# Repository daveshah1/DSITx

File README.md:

# MIPI DSI FPGA LCD Interface

This is a work-in-progress core to interface advanced MIPI DSI displays with a Xilinx
7-series FPGA. The current display target is the Sony Z5 Premium LCD (AUO H546UAN01.0 or Sharp LS055D1SX05)
which is a  5.5" 4k (2160x3840) LCD. At the moment I am running it in a mode where content is upscaled by the panel
from 1080x1920, as 4k content must be compressed using VESA DSC or Qualcomm FBC. I am working on an encoder for the former.

The only DSI mode currently supported is Command Mode, Video Mode is still being worked on and is not as well documented for the target panels. This
panel works in dual DSI mode, so two transmitters are used each transmitting half of each line. Single-link command mode panels would also work, with
by only instantiating one `dsi_tx_cmd_mode_top`.

A demo project is included for the afforementioned panel and config. It was designed for an FMC breakout board I've built for the Genesys 2 development
board with a Kintex-7 FPGA. Unfortunately a signal integrity issue on this board means I have to run the DSI link at its lowest rate, 200Mbps, which limits
the framerate to about 30fps. Nonetheless, the design files for this board are included if you want a circuit to run the display, although in any system
you develop the MIPI DSI translator resistors should be located much closer to the FPGA to avoid the issues I've had.

The final intended use of this interface is for a larger project I am working on, the [openMixR](https://github.com/daveshah1/openMixR) 4k headset.

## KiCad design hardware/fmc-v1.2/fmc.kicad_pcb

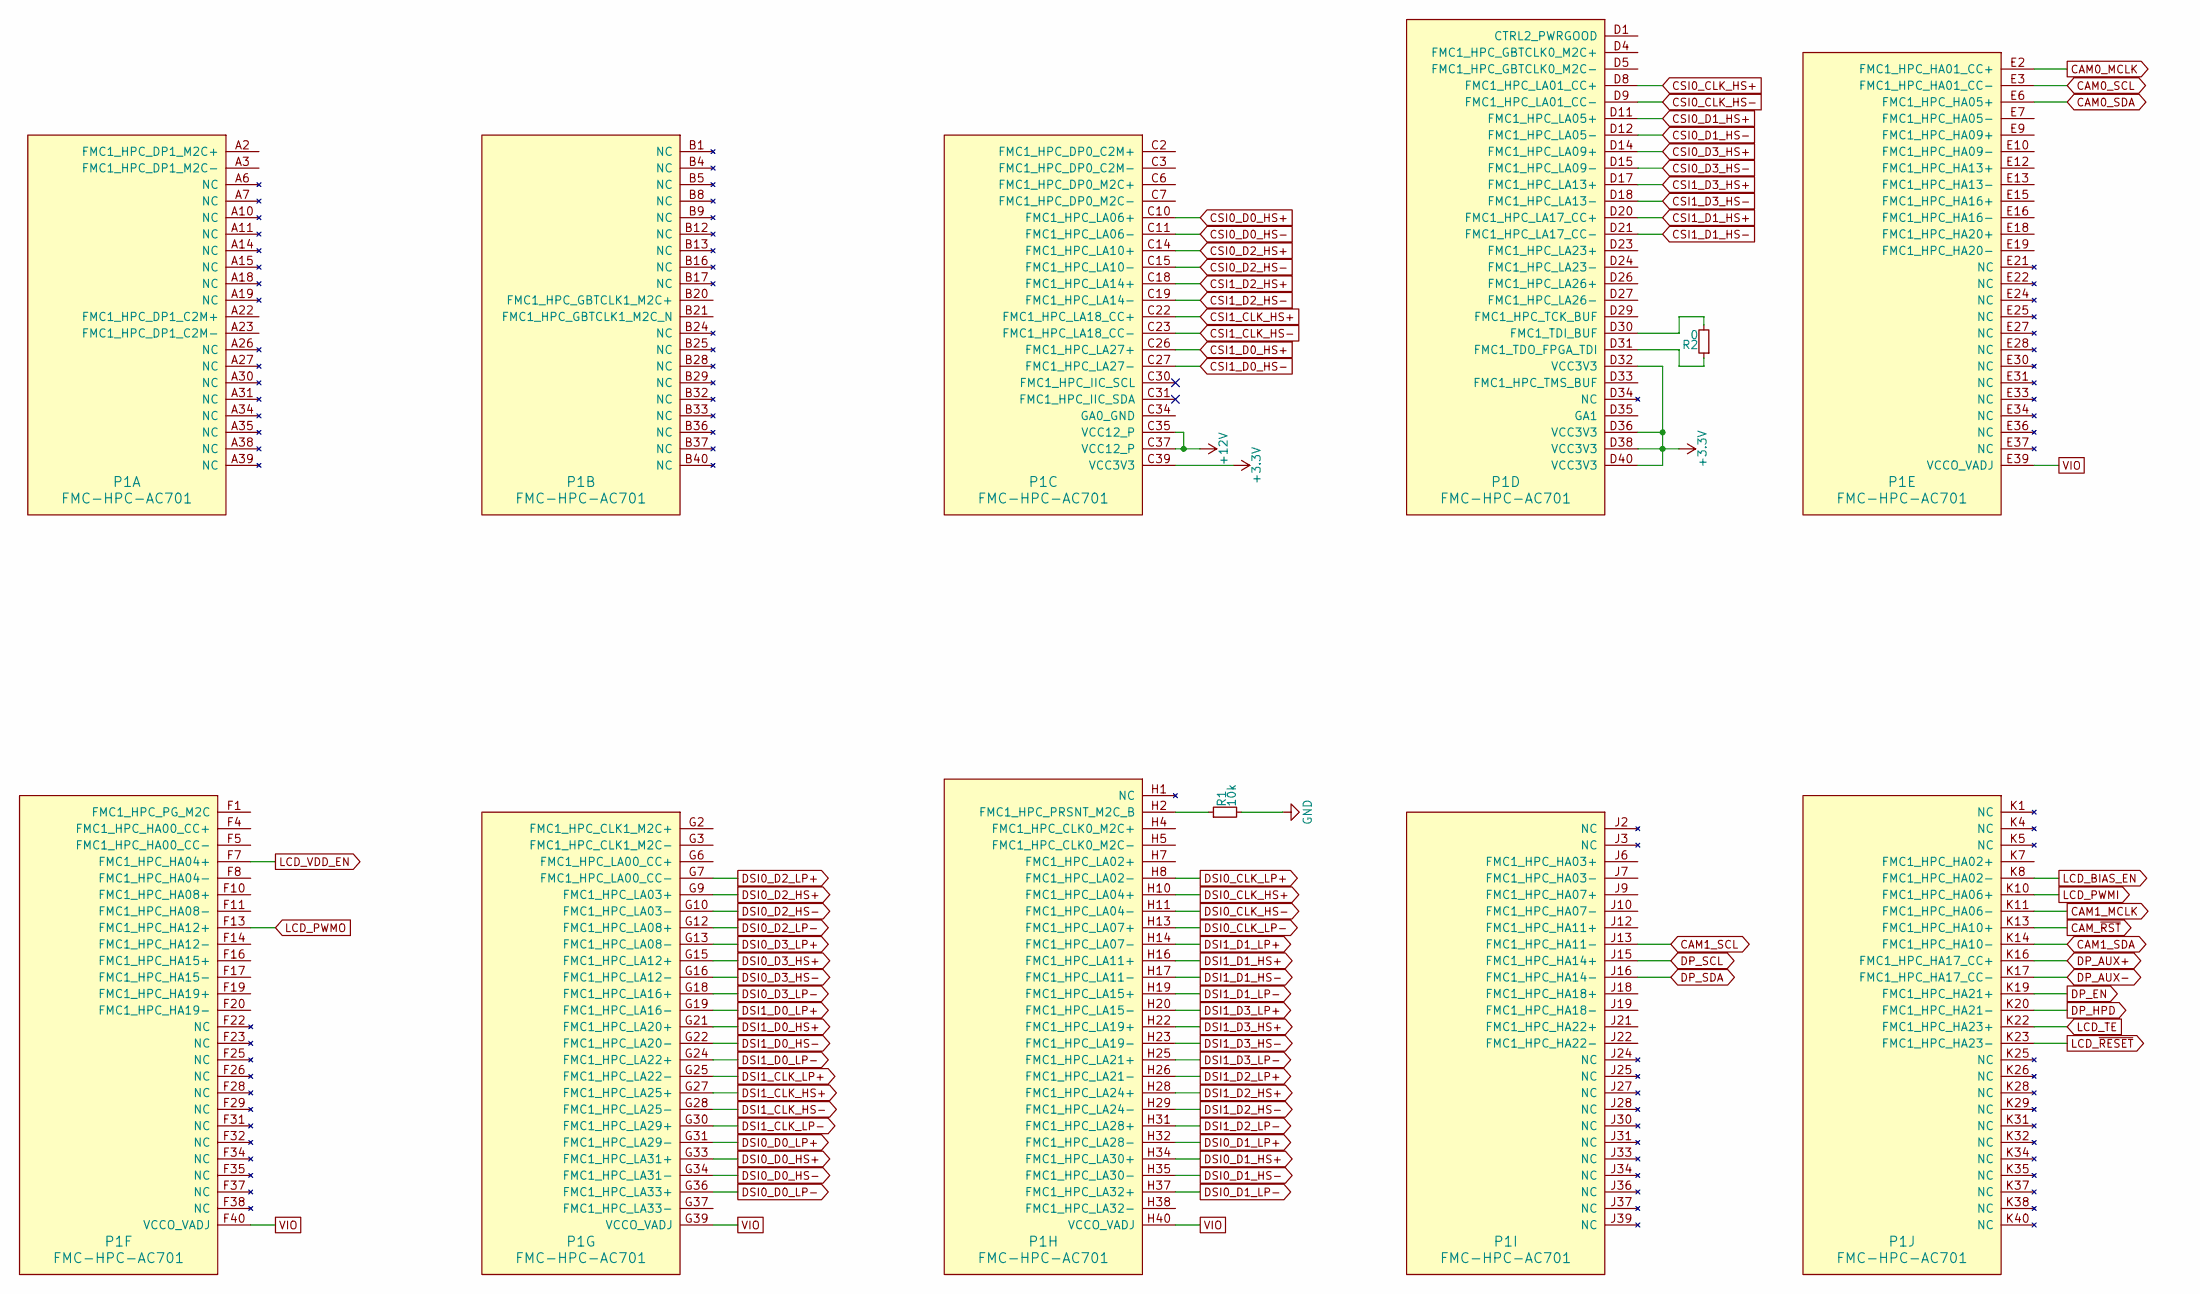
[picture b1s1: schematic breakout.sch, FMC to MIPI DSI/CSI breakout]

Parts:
P1: FMC-HPC-AC701; ASP-134488-01
R1: 10k; R_0402
R2: 0; R_0402

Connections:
+3V3: P1.C39 (VCC3V3), P1.D32 (VCC3V3), P1.D36 (VCC3V3), P1.D38 (VCC3V3), P1.D40 (VCC3V3); also elsewhere on the board
+12V: P1.C35 (VCC12_P), P1.C37 (VCC12_P); also elsewhere on the board
CAM0_MCLK: P1.E2 (FMC1_HPC_HA01_CC+); also elsewhere on the board
CAM0_SCL: P1.E3 (FMC1_HPC_HA01_CC-); also elsewhere on the board
CAM0_SDA: P1.E6 (FMC1_HPC_HA05+); also elsewhere on the board
CAM1_MCLK: P1.K11 (FMC1_HPC_HA06-); also elsewhere on the board
CAM1_SCL: P1.J13 (FMC1_HPC_HA11-); also elsewhere on the board
CAM1_SDA: P1.K14 (FMC1_HPC_HA10-); also elsewhere on the board
CAM_~RST: P1.K13 (FMC1_HPC_HA10+); also elsewhere on the board
CSI0_CLK_HS+: P1.D8 (FMC1_HPC_LA01_CC+); also elsewhere on the board
CSI0_CLK_HS-: P1.D9 (FMC1_HPC_LA01_CC-); also elsewhere on the board
CSI0_D0_HS+: P1.C10 (FMC1_HPC_LA06+); also elsewhere on the board
CSI0_D0_HS-: P1.C11 (FMC1_HPC_LA06-); also elsewhere on the board
CSI0_D1_HS+: P1.D11 (FMC1_HPC_LA05+); also elsewhere on the board
CSI0_D1_HS-: P1.D12 (FMC1_HPC_LA05-); also elsewhere on the board
CSI0_D2_HS+: P1.C14 (FMC1_HPC_LA10+); also elsewhere on the board
CSI0_D2_HS-: P1.C15 (FMC1_HPC_LA10-); also elsewhere on the board
CSI0_D3_HS+: P1.D14 (FMC1_HPC_LA09+); also elsewhere on the board
CSI0_D3_HS-: P1.D15 (FMC1_HPC_LA09-); also elsewhere on the board
CSI1_CLK_HS+: P1.C22 (FMC1_HPC_LA18_CC+); also elsewhere on the board
CSI1_CLK_HS-: P1.C23 (FMC1_HPC_LA18_CC-); also elsewhere on the board
CSI1_D0_HS+: P1.C26 (FMC1_HPC_LA27+); also elsewhere on the board
CSI1_D0_HS-: P1.C27 (FMC1_HPC_LA27-); also elsewhere on the board
CSI1_D1_HS+: P1.D20 (FMC1_HPC_LA17_CC+); also elsewhere on the board
CSI1_D1_HS-: P1.D21 (FMC1_HPC_LA17_CC-); also elsewhere on the board
CSI1_D2_HS+: P1.C18 (FMC1_HPC_LA14+); also elsewhere on the board
CSI1_D2_HS-: P1.C19 (FMC1_HPC_LA14-); also elsewhere on the board
CSI1_D3_HS+: P1.D17 (FMC1_HPC_LA13+); also elsewhere on the board
CSI1_D3_HS-: P1.D18 (FMC1_HPC_LA13-); also elsewhere on the board
DSI0_CLK_HS+: P1.H10 (FMC1_HPC_LA04+); also elsewhere on the board
DSI0_CLK_HS-: P1.H11 (FMC1_HPC_LA04-); also elsewhere on the board
DSI0_CLK_LP+: P1.H8 (FMC1_HPC_LA02-); also elsewhere on the board
DSI0_CLK_LP-: P1.H13 (FMC1_HPC_LA07+); also elsewhere on the board
DSI0_D0_HS+: P1.G33 (FMC1_HPC_LA31+); also elsewhere on the board
DSI0_D0_HS-: P1.G34 (FMC1_HPC_LA31-); also elsewhere on the board
DSI0_D0_LP+: P1.G31 (FMC1_HPC_LA29-); also elsewhere on the board
DSI0_D0_LP-: P1.G36 (FMC1_HPC_LA33+); also elsewhere on the board
DSI0_D1_HS+: P1.H34 (FMC1_HPC_LA30+); also elsewhere on the board
DSI0_D1_HS-: P1.H35 (FMC1_HPC_LA30-); also elsewhere on the board
DSI0_D1_LP+: P1.H32 (FMC1_HPC_LA28-); also elsewhere on the board
DSI0_D1_LP-: P1.H37 (FMC1_HPC_LA32+); also elsewhere on the board
DSI0_D2_HS+: P1.G9 (FMC1_HPC_LA03+); also elsewhere on the board
DSI0_D2_HS-: P1.G10 (FMC1_HPC_LA03-); also elsewhere on the board
DSI0_D2_LP+: P1.G7 (FMC1_HPC_LA00_CC-); also elsewhere on the board
DSI0_D2_LP-: P1.G12 (FMC1_HPC_LA08+); also elsewhere on the board
DSI0_D3_HS+: P1.G15 (FMC1_HPC_LA12+); also elsewhere on the board
DSI0_D3_HS-: P1.G16 (FMC1_HPC_LA12-); also elsewhere on the board
DSI0_D3_LP+: P1.G13 (FMC1_HPC_LA08-); also elsewhere on the board
DSI0_D3_LP-: P1.G18 (FMC1_HPC_LA16+); also elsewhere on the board
DSI1_CLK_HS+: P1.G27 (FMC1_HPC_LA25+); also elsewhere on the board
DSI1_CLK_HS-: P1.G28 (FMC1_HPC_LA25-); also elsewhere on the board
DSI1_CLK_LP+: P1.G25 (FMC1_HPC_LA22-); also elsewhere on the board
DSI1_CLK_LP-: P1.G30 (FMC1_HPC_LA29+); also elsewhere on the board
DSI1_D0_HS+: P1.G21 (FMC1_HPC_LA20+); also elsewhere on the board
DSI1_D0_HS-: P1.G22 (FMC1_HPC_LA20-); also elsewhere on the board
DSI1_D0_LP+: P1.G19 (FMC1_HPC_LA16-); also elsewhere on the board
DSI1_D0_LP-: P1.G24 (FMC1_HPC_LA22+); also elsewhere on the board
DSI1_D1_HS+: P1.H16 (FMC1_HPC_LA11+); also elsewhere on the board
DSI1_D1_HS-: P1.H17 (FMC1_HPC_LA11-); also elsewhere on the board
DSI1_D1_LP+: P1.H14 (FMC1_HPC_LA07-); also elsewhere on the board
DSI1_D1_LP-: P1.H19 (FMC1_HPC_LA15+); also elsewhere on the board
DSI1_D2_HS+: P1.H28 (FMC1_HPC_LA24+); also elsewhere on the board
DSI1_D2_HS-: P1.H29 (FMC1_HPC_LA24-); also elsewhere on the board
DSI1_D2_LP+: P1.H26 (FMC1_HPC_LA21-); also elsewhere on the board
DSI1_D2_LP-: P1.H31 (FMC1_HPC_LA28+); also elsewhere on the board
DSI1_D3_HS+: P1.H22 (FMC1_HPC_LA19+); also elsewhere on the board
DSI1_D3_HS-: P1.H23 (FMC1_HPC_LA19-); also elsewhere on the board
DSI1_D3_LP+: P1.H20 (FMC1_HPC_LA15-); also elsewhere on the board
DSI1_D3_LP-: P1.H25 (FMC1_HPC_LA21+); also elsewhere on the board
GND: R1.2; also elsewhere on the board
LCD_BIAS_EN: P1.K8 (FMC1_HPC_HA02-); also elsewhere on the board
LCD_PWMI: P1.K10 (FMC1_HPC_HA06+); also elsewhere on the board
LCD_TE: P1.K22 (FMC1_HPC_HA23+); also elsewhere on the board
LCD_VDD_EN: P1.F7 (FMC1_HPC_HA04+); also elsewhere on the board
LCD_~RESET: P1.K23 (FMC1_HPC_HA23-); also elsewhere on the board
unnamed: P1.D30 (FMC1_TDI_BUF), R2.2
unnamed: P1.D31 (FMC1_TDO_FPGA_TDI), R2.1
unnamed: P1.H2 (FMC1_HPC_PRSNT_M2C_B), R1.1
VIO: P1.E39 (VCCO_VADJ), P1.F40 (VCCO_VADJ), P1.G39 (VCCO_VADJ), P1.H40 (VCCO_VADJ); also elsewhere on the board

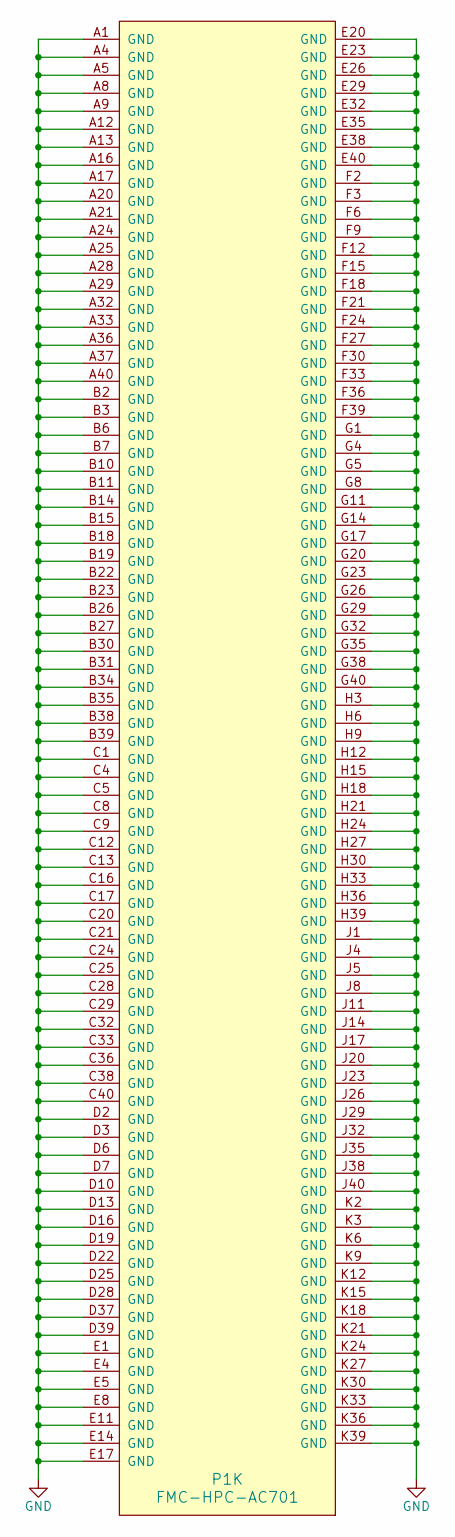
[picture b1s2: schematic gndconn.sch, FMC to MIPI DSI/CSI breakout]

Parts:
P1: FMC-HPC-AC701; ASP-134488-01

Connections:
GND: P1.A1 (GND), P1.A4 (GND), P1.A5 (GND), P1.A8 (GND), P1.A9 (GND), P1.A12 (GND), P1.A13 (GND), P1.A16 (GND), P1.A17 (GND), P1.A20 (GND), P1.A21 (GND), P1.A24 (GND), P1.A25 (GND), P1.A28 (GND), P1.A29 (GND), P1.A32 (GND), P1.A33 (GND), P1.A36 (GND), P1.A37 (GND), P1.A40 (GND), P1.B2 (GND), P1.B3 (GND), P1.B6 (GND), P1.B7 (GND), P1.B10 (GND), P1.B11 (GND), P1.B14 (GND), P1.B15 (GND), P1.B18 (GND), P1.B19 (GND), P1.B22 (GND), P1.B23 (GND), P1.B26 (GND), P1.B27 (GND), P1.B30 (GND), P1.B31 (GND), P1.B34 (GND), P1.B35 (GND), P1.B38 (GND), P1.B39 (GND), P1.C1 (GND), P1.C4 (GND), P1.C5 (GND), P1.C8 (GND), P1.C9 (GND), P1.C12 (GND), P1.C13 (GND), P1.C16 (GND), P1.C17 (GND), P1.C20 (GND), P1.C21 (GND), P1.C24 (GND), P1.C25 (GND), P1.C28 (GND), P1.C29 (GND), P1.C32 (GND), P1.C33 (GND), P1.C36 (GND), P1.C38 (GND), P1.C40 (GND), P1.D2 (GND), P1.D3 (GND), P1.D6 (GND), P1.D7 (GND), P1.D10 (GND), P1.D13 (GND), P1.D16 (GND), P1.D19 (GND), P1.D22 (GND), P1.D25 (GND), P1.D28 (GND), P1.D37 (GND), P1.D39 (GND), P1.E1 (GND), P1.E4 (GND), P1.E5 (GND), P1.E8 (GND), P1.E11 (GND), P1.E14 (GND), P1.E17 (GND), P1.E20 (GND), P1.E23 (GND), P1.E26 (GND), P1.E29 (GND), P1.E32 (GND), P1.E35 (GND), P1.E38 (GND), P1.E40 (GND), P1.F2 (GND), P1.F3 (GND), P1.F6 (GND), P1.F9 (GND), P1.F12 (GND), P1.F15 (GND), P1.F18 (GND), P1.F21 (GND), P1.F24 (GND), P1.F27 (GND), P1.F30 (GND), P1.F33 (GND), P1.F36 (GND), P1.F39 (GND), P1.G1 (GND), P1.G4 (GND), P1.G5 (GND), P1.G8 (GND), P1.G11 (GND), P1.G14 (GND), P1.G17 (GND), P1.G20 (GND), P1.G23 (GND), P1.G26 (GND), P1.G29 (GND), P1.G32 (GND), P1.G35 (GND), P1.G38 (GND), P1.G40 (GND), P1.H3 (GND), P1.H6 (GND), P1.H9 (GND), P1.H12 (GND), P1.H15 (GND), P1.H18 (GND), P1.H21 (GND), P1.H24 (GND), P1.H27 (GND), P1.H30 (GND), P1.H33 (GND), P1.H36 (GND), P1.H39 (GND), P1.J1 (GND), P1.J4 (GND), P1.J5 (GND), P1.J8 (GND), P1.J11 (GND), P1.J14 (GND), P1.J17 (GND), P1.J20 (GND), P1.J23 (GND), P1.J26 (GND), P1.J29 (GND), P1.J32 (GND), P1.J35 (GND), P1.J38 (GND), P1.J40 (GND), P1.K2 (GND), P1.K3 (GND), P1.K6 (GND), P1.K9 (GND), P1.K12 (GND), P1.K15 (GND), P1.K18 (GND), P1.K21 (GND), P1.K24 (GND), P1.K27 (GND), P1.K30 (GND), P1.K33 (GND), P1.K36 (GND), P1.K39 (GND); also elsewhere on the board

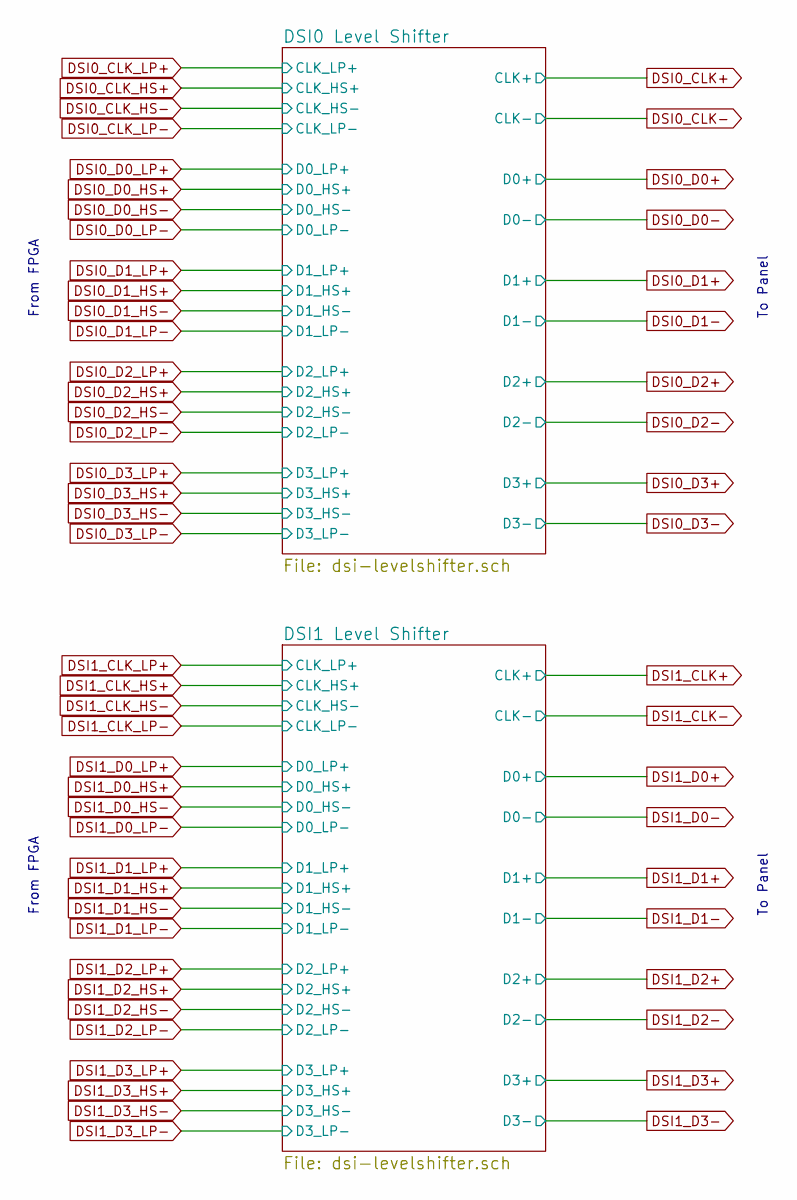
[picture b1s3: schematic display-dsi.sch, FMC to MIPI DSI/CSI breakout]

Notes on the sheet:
From FPGA
To Panel

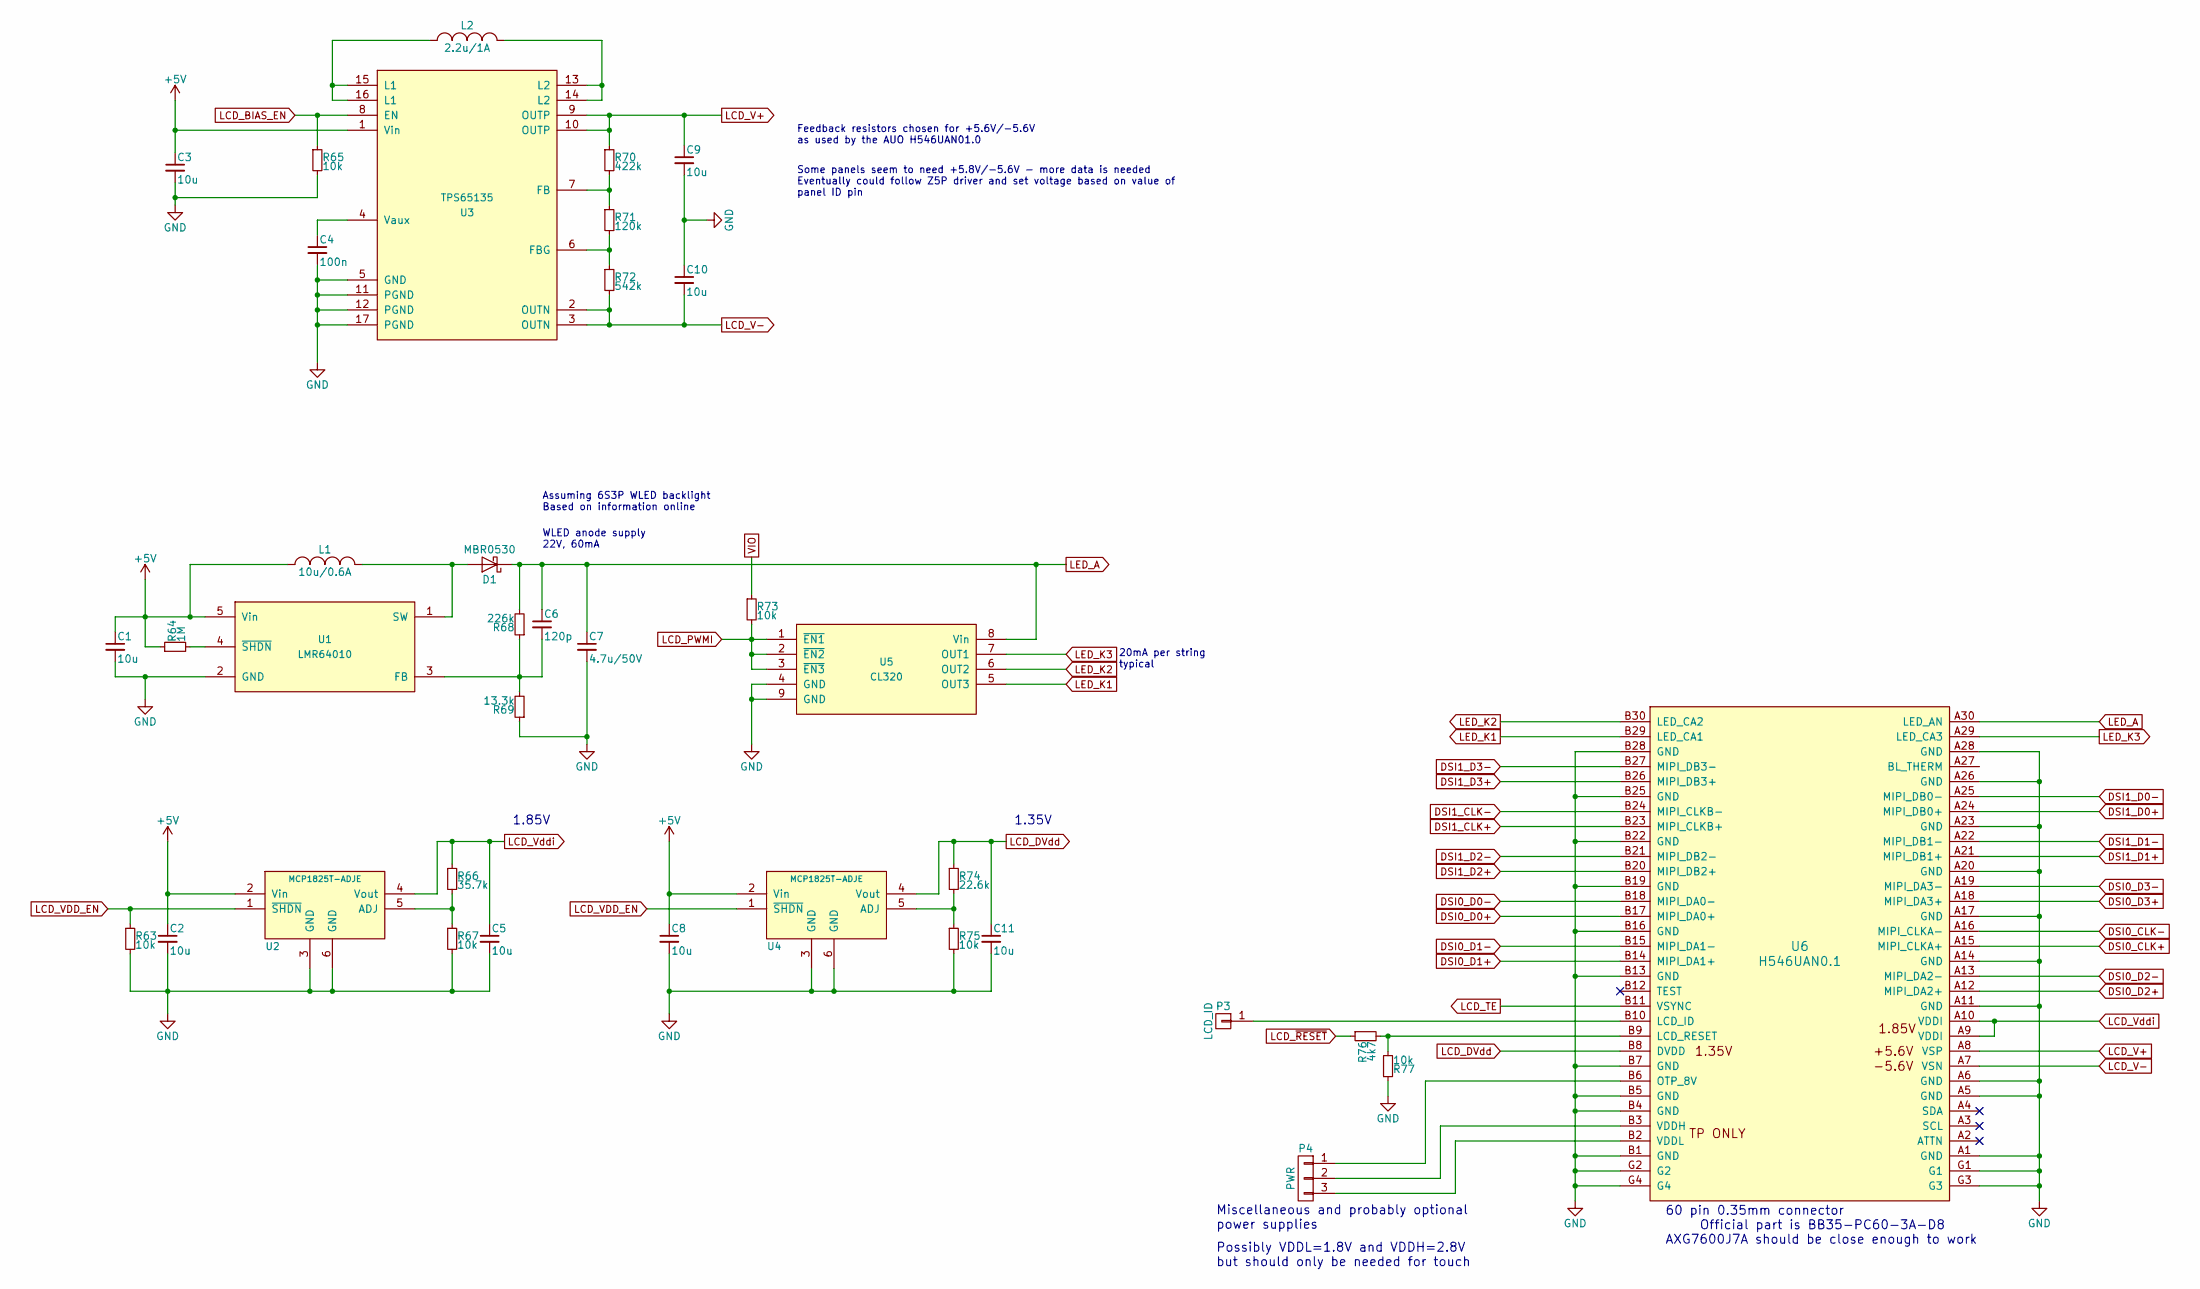
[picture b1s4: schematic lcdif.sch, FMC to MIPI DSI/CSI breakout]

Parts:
C1, C2, C3, C5, C8, C9, C10, C11: 10u; C_0805
C4: 100n; C_0402
C6: 120p; C_0402
C7: 4.7u/50V; C_1206
D1: MBR0530; SOD-123
L1: 10u/0.6A; Neosid_Inductor_SM-NE29_SMD1008
L2: 2.2u/1A; Neosid_Inductor_SM-NE29_SMD1008
P3: LCD_ID; Measurement_Point_Round-SMD-Pad_Small
P4: PWR; Pin_Header_Straight_1x03
R63, R65, R67, R73, R75, R77: 10k; R_0402
R64: 1M; R_0402
R66: 35.7k; R_0402
R68: 226k; R_0402
R69: 13.3k; R_0402
R70: 422k; R_0402
R71: 120k; R_0402
R72: 542k; R_0402
R74: 22.6k; R_0402
R76: 4k7; R_0402
U1: LMR64010; SOT-23-5
U2, U4: MCP1825T-ADJE; SOT-223-6
U3: TPS65135; QFN-16-1EP_3x3mm_Pitch0.5mm
U5: CL320; SOIC-8-1EP_3.9x4.9mm_Pitch1.27mm
U6: H546UAN0.1; 60pin-0.35mm

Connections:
+5V: C1.1, C2.1, C3.1, C8.1, L1.1, R64.1, U1.5 (Vin), U2.2 (Vin), U3.1 (Vin), U4.2 (Vin); also elsewhere on the board
DSI0_CLK+: U6.A15 (MIPI_CLKA+); also elsewhere on the board
DSI0_CLK-: U6.A16 (MIPI_CLKA-); also elsewhere on the board
DSI0_D0+: U6.B17 (MIPI_DA0+); also elsewhere on the board
DSI0_D0-: U6.B18 (MIPI_DA0-); also elsewhere on the board
DSI0_D1+: U6.B14 (MIPI_DA1+); also elsewhere on the board
DSI0_D1-: U6.B15 (MIPI_DA1-); also elsewhere on the board
DSI0_D2+: U6.A12 (MIPI_DA2+); also elsewhere on the board
DSI0_D2-: U6.A13 (MIPI_DA2-); also elsewhere on the board
DSI0_D3+: U6.A18 (MIPI_DA3+); also elsewhere on the board
DSI0_D3-: U6.A19 (MIPI_DA3-); also elsewhere on the board
DSI1_CLK+: U6.B23 (MIPI_CLKB+); also elsewhere on the board
DSI1_CLK-: U6.B24 (MIPI_CLKB-); also elsewhere on the board
DSI1_D0+: U6.A24 (MIPI_DB0+); also elsewhere on the board
DSI1_D0-: U6.A25 (MIPI_DB0-); also elsewhere on the board
DSI1_D1+: U6.A21 (MIPI_DB1+); also elsewhere on the board
DSI1_D1-: U6.A22 (MIPI_DB1-); also elsewhere on the board
DSI1_D2+: U6.B20 (MIPI_DB2+); also elsewhere on the board
DSI1_D2-: U6.B21 (MIPI_DB2-); also elsewhere on the board
DSI1_D3+: U6.B26 (MIPI_DB3+); also elsewhere on the board
DSI1_D3-: U6.B27 (MIPI_DB3-); also elsewhere on the board
GND: C1.2, C2.2, C3.2, C4.2, C5.2, C7.2, C8.2, C9.2, C10.1, C11.2, R63.2, R65.2, R67.2, R69.1, R75.2, R77.1, U1.2 (GND), U2.3 (GND), U2.6 (GND), U3.5 (GND), U3.11 (PGND), U3.12 (PGND), U3.17 (PGND), U4.3 (GND), U4.6 (GND), U5.4 (GND), U5.9 (GND), U6.A1 (GND), U6.A5 (GND), U6.A6 (GND), U6.A11 (GND), U6.A14 (GND), U6.A17 (GND), U6.A20 (GND), U6.A23 (GND), U6.A26 (GND), U6.A28 (GND), U6.B1 (GND), U6.B4 (GND), U6.B5 (GND), U6.B7 (GND), U6.B13 (GND), U6.B16 (GND), U6.B19 (GND), U6.B22 (GND), U6.B25 (GND), U6.B28 (GND), U6.G1, U6.G2, U6.G3, U6.G4; also elsewhere on the board
LCD_BIAS_EN: R65.1, U3.8 (EN); also elsewhere on the board
LCD_DVdd: C11.1, R74.1, U4.4 (Vout), U6.B8 (DVDD)
LCD_PWMI: R73.2, U5.1 (~EN1), U5.2 (~EN2), U5.3 (~EN3); also elsewhere on the board
LCD_TE: U6.B11 (VSYNC); also elsewhere on the board
LCD_V+: C9.1, R70.1, U3.9 (OUTP), U3.10 (OUTP), U6.A8 (VSP)
LCD_V-: C10.2, R72.2, U3.2 (OUTN), U3.3 (OUTN), U6.A7 (VSN)
LCD_VDD_EN: R63.1, U2.1 (~SHDN), U4.1 (~SHDN); also elsewhere on the board
LCD_Vddi: C5.1, R66.1, U2.4 (Vout), U6.A9 (VDDI), U6.A10 (VDDI)
LCD_~RESET: R76.1; also elsewhere on the board
LED_A: C6.1, C7.1, D1.1 (K), R68.2, U5.8 (Vin), U6.A30 (LED_AN)
LED_K1: U5.5 (OUT3), U6.B29 (LED_CA1)
LED_K2: U5.6 (OUT2), U6.B30 (LED_CA2)
LED_K3: U5.7 (OUT1), U6.A29 (LED_CA3)
unnamed: C4.1, U3.4 (Vaux)
unnamed: C6.2, R68.1, R69.2, U1.3 (FB)
unnamed: D1.2 (A), L1.2, U1.1 (SW)
unnamed: L2.1, U3.15 (L1), U3.16 (L1)
unnamed: L2.2, U3.13 (L2), U3.14 (L2)
unnamed: P3.1, U6.B10 (LCD_ID)
unnamed: P4.1, U6.B6 (OTP_8V)
unnamed: P4.2, U6.B3 (VDDH)
unnamed: P4.3, U6.B2 (VDDL)
unnamed: R64.2, U1.4 (~SHDN)
unnamed: R66.2, R67.1, U2.5 (ADJ)
unnamed: R70.2, R71.1, U3.7 (FB)
unnamed: R71.2, R72.1, U3.6 (FBG)
unnamed: R74.2, R75.1, U4.5 (ADJ)
unnamed: R76.2, R77.2, U6.B9 (LCD_RESET)
VIO: R73.1; also elsewhere on the board

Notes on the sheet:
Feedback resistors chosen for +5.6V/-5.6V as used by the AUO H546UAN01.0
Some panels seem to need +5.8V/-5.6V - more data is needed Eventually could follow Z5P driver and set voltage based on value of panel ID pin
WLED anode supply 22V, 60mA
Assuming 6S3P WLED backlight Based on information online
20mA per string typical
1.85V
1.35V
Miscellaneous and probably optional power supplies
Possibly VDDL=1.8V and VDDH=2.8V but should only be needed for touch
60 pin 0.35mm connector Official part is BB35-PC60-3A-D8 AXG7600J7A should be close enough to work

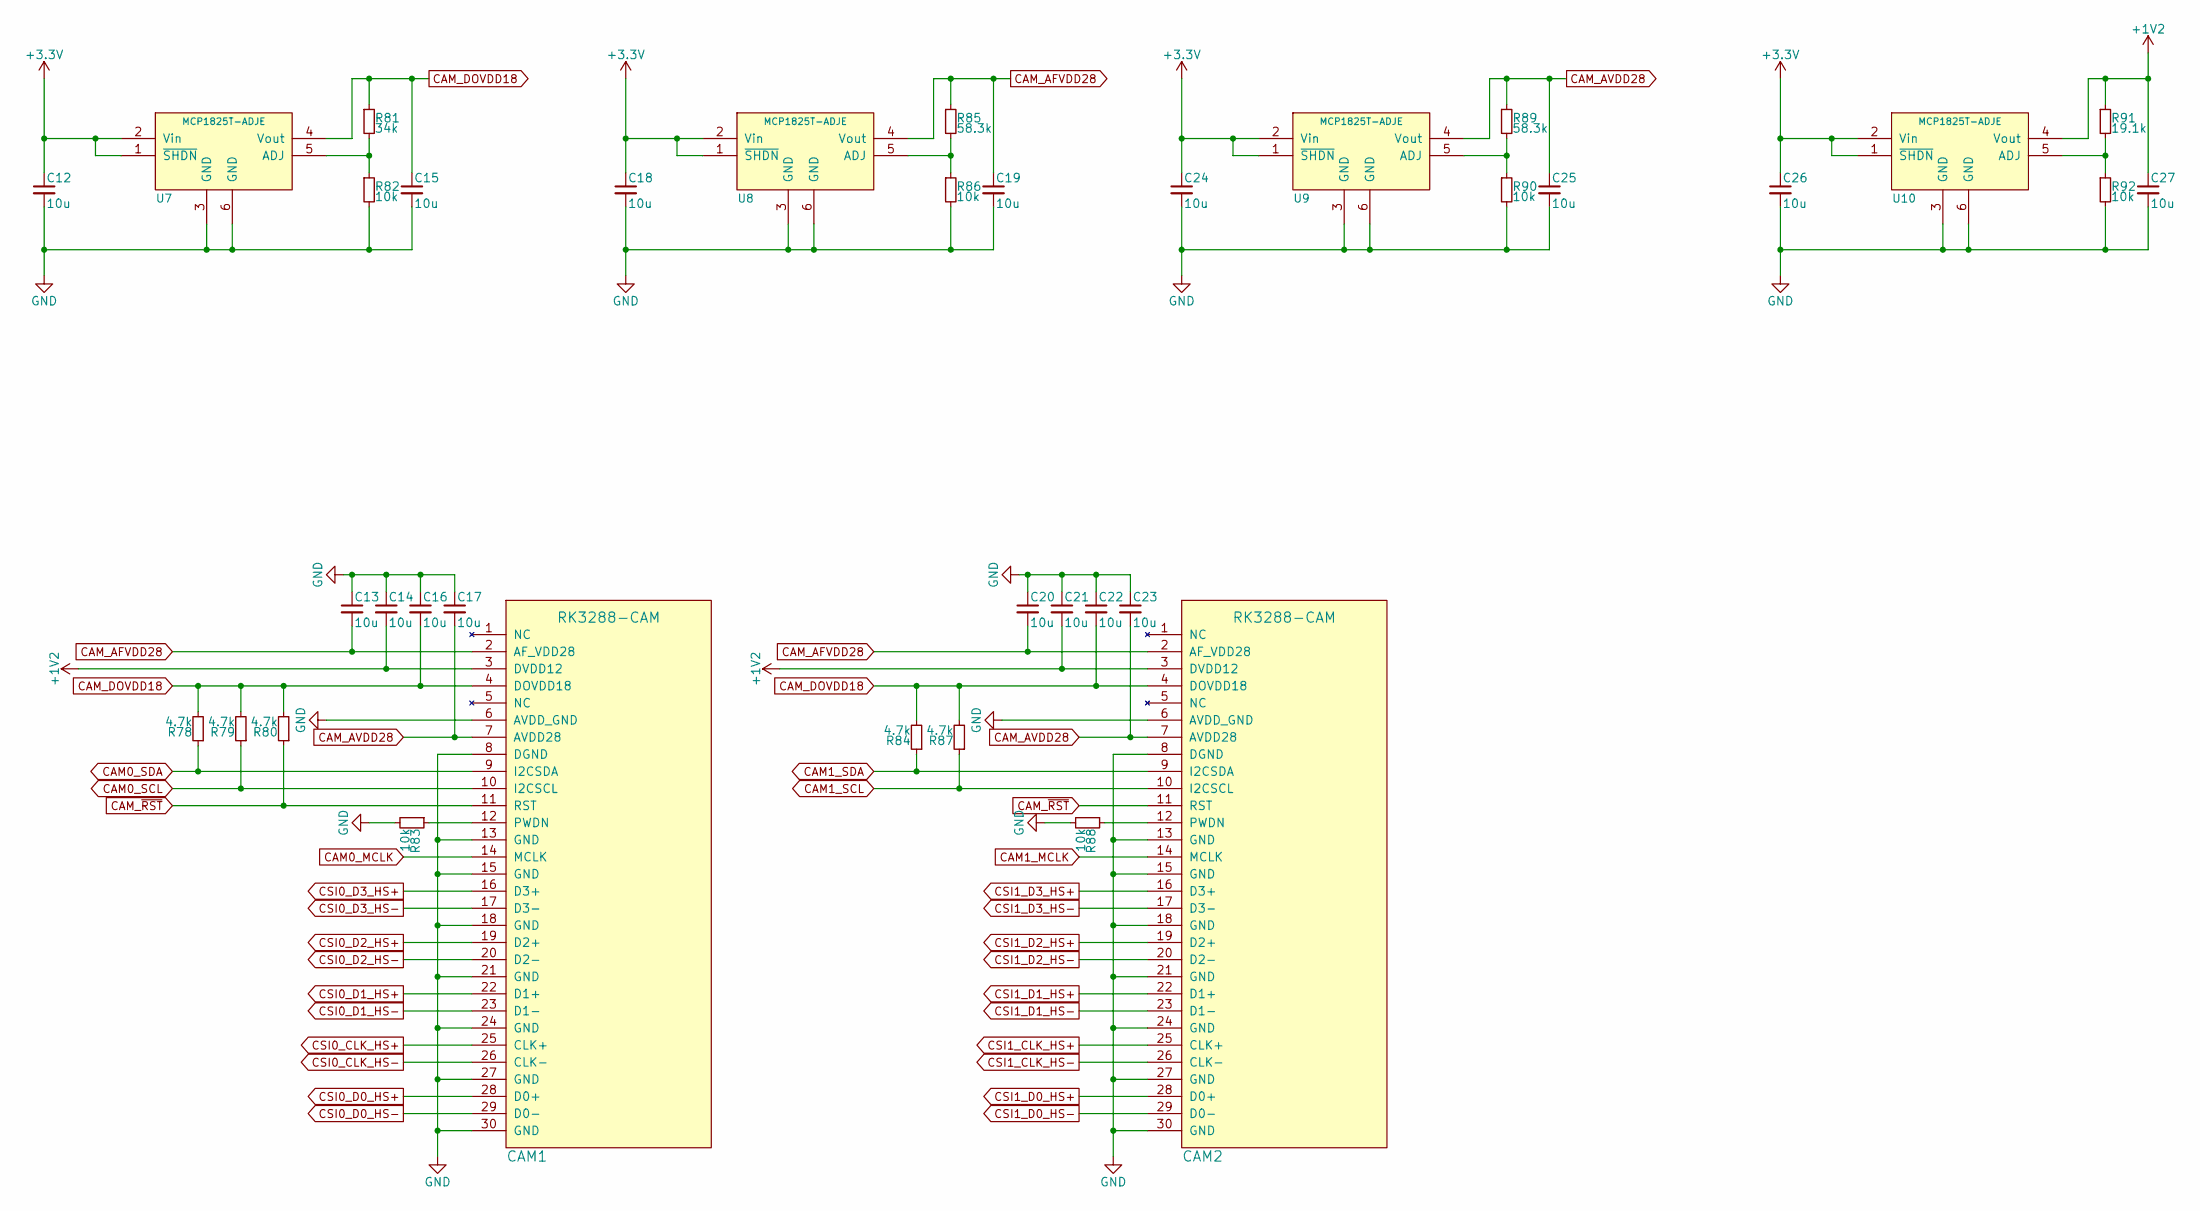
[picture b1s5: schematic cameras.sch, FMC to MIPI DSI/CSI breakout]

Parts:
C12, C13, C14, C15, C16, C17, C18, C19, C20, C21, C22, C23, C24, C25, C26, C27: 10u; C_0805
CAM1, CAM2: RK3288-CAM; 3-1734592-0
R78, R79, R80, R84, R87: 4.7k; R_0402
R81: 34k; R_0402
R82, R83, R86, R88, R90, R92: 10k; R_0402
R85, R89: 58.3k; R_0402
R91: 19.1k; R_0402
U7, U8, U9, U10: MCP1825T-ADJE; SOT-223-6

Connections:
+1V2: C14.2, C21.2, C27.1, CAM1.3 (DVDD12), CAM2.3 (DVDD12), R91.1, U10.4 (Vout)
+3V3: C12.1, C18.1, C24.1, C26.1, U7.1 (~SHDN), U7.2 (Vin), U8.1 (~SHDN), U8.2 (Vin), U9.1 (~SHDN), U9.2 (Vin), U10.1 (~SHDN), U10.2 (Vin); also elsewhere on the board
CAM0_MCLK: CAM1.14 (MCLK); also elsewhere on the board
CAM0_SCL: CAM1.10 (I2CSCL), R79.1; also elsewhere on the board
CAM0_SDA: CAM1.9 (I2CSDA), R78.1; also elsewhere on the board
CAM1_MCLK: CAM2.14 (MCLK); also elsewhere on the board
CAM1_SCL: CAM2.10 (I2CSCL), R87.1; also elsewhere on the board
CAM1_SDA: CAM2.9 (I2CSDA), R84.1; also elsewhere on the board
CAM_AFVDD28: C13.2, C19.1, C20.2, CAM1.2 (AF_VDD28), CAM2.2 (AF_VDD28), R85.1, U8.4 (Vout)
CAM_AVDD28: C17.2, C23.2, C25.1, CAM1.7 (AVDD28), CAM2.7 (AVDD28), R89.1, U9.4 (Vout)
CAM_DOVDD18: C15.1, C16.2, C22.2, CAM1.4 (DOVDD18), CAM2.4 (DOVDD18), R78.2, R79.2, R80.2, R81.1, R84.2, R87.2, U7.4 (Vout)
CAM_~RST: CAM1.11 (RST), CAM2.11 (RST), R80.1; also elsewhere on the board
CSI0_CLK_HS+: CAM1.25 (CLK+); also elsewhere on the board
CSI0_CLK_HS-: CAM1.26 (CLK-); also elsewhere on the board
CSI0_D0_HS+: CAM1.28 (D0+); also elsewhere on the board
CSI0_D0_HS-: CAM1.29 (D0-); also elsewhere on the board
CSI0_D1_HS+: CAM1.22 (D1+); also elsewhere on the board
CSI0_D1_HS-: CAM1.23 (D1-); also elsewhere on the board
CSI0_D2_HS+: CAM1.19 (D2+); also elsewhere on the board
CSI0_D2_HS-: CAM1.20 (D2-); also elsewhere on the board
CSI0_D3_HS+: CAM1.16 (D3+); also elsewhere on the board
CSI0_D3_HS-: CAM1.17 (D3-); also elsewhere on the board
CSI1_CLK_HS+: CAM2.25 (CLK+); also elsewhere on the board
CSI1_CLK_HS-: CAM2.26 (CLK-); also elsewhere on the board
CSI1_D0_HS+: CAM2.28 (D0+); also elsewhere on the board
CSI1_D0_HS-: CAM2.29 (D0-); also elsewhere on the board
CSI1_D1_HS+: CAM2.22 (D1+); also elsewhere on the board
CSI1_D1_HS-: CAM2.23 (D1-); also elsewhere on the board
CSI1_D2_HS+: CAM2.19 (D2+); also elsewhere on the board
CSI1_D2_HS-: CAM2.20 (D2-); also elsewhere on the board
CSI1_D3_HS+: CAM2.16 (D3+); also elsewhere on the board
CSI1_D3_HS-: CAM2.17 (D3-); also elsewhere on the board
GND: C12.2, C13.1, C14.1, C15.2, C16.1, C17.1, C18.2, C19.2, C20.1, C21.1, C22.1, C23.1, C24.2, C25.2, C26.2, C27.2, CAM1.6 (AVDD_GND), CAM1.8 (DGND), CAM1.13 (GND), CAM1.15 (GND), CAM1.18 (GND), CAM1.21 (GND), CAM1.24 (GND), CAM1.27 (GND), CAM1.30 (GND), CAM2.6 (AVDD_GND), CAM2.8 (DGND), CAM2.13 (GND), CAM2.15 (GND), CAM2.18 (GND), CAM2.21 (GND), CAM2.24 (GND), CAM2.27 (GND), CAM2.30 (GND), R82.2, R83.2, R86.2, R88.2, R90.2, R92.2, U7.3 (GND), U7.6 (GND), U8.3 (GND), U8.6 (GND), U9.3 (GND), U9.6 (GND), U10.3 (GND), U10.6 (GND); also elsewhere on the board
unnamed: CAM1.12 (PWDN), R83.1
unnamed: CAM2.12 (PWDN), R88.1
unnamed: R81.2, R82.1, U7.5 (ADJ)
unnamed: R85.2, R86.1, U8.5 (ADJ)
unnamed: R89.2, R90.1, U9.5 (ADJ)
unnamed: R91.2, R92.1, U10.5 (ADJ)

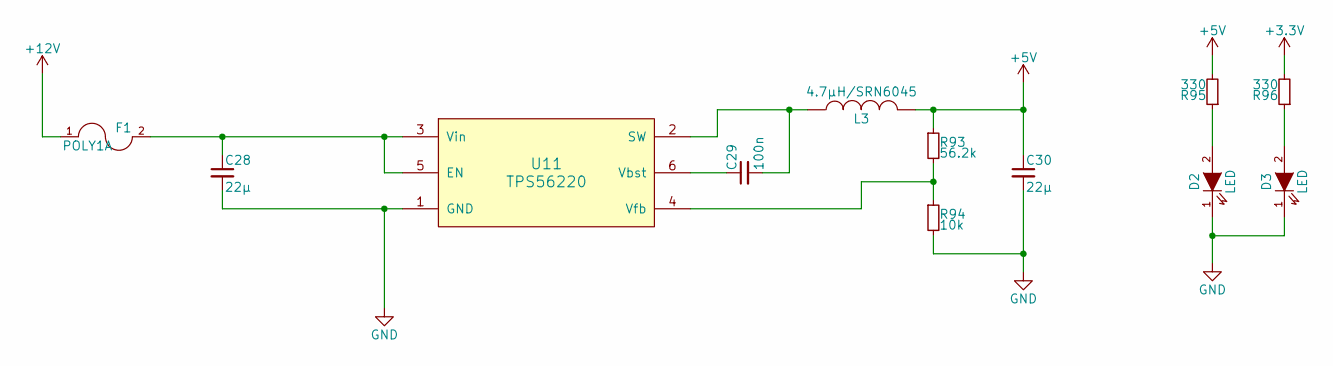
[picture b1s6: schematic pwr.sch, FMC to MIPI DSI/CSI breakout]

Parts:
C28, C30: 22µ; C_1206
C29: 100n; C_0402
D2, D3: LED; LED_0805
F1: POLY1A; Fuse_SMD1206_Reflow
L3: 4.7µH/SRN6045; SRN6045
R93: 56.2k; R_0402
R94: 10k; R_0402
R95, R96: 330; R_0402
U11: TPS56220; SOT-23-6

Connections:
+3V3: R96.2; also elsewhere on the board
+5V: C30.1, L3.2, R93.1, R95.2; also elsewhere on the board
+12V: F1.1; also elsewhere on the board
GND: C28.2, C30.2, D2.1 (K), D3.1 (K), R94.2, U11.1 (GND); also elsewhere on the board
unnamed: C28.1, F1.2, U11.3 (Vin), U11.5 (EN)
unnamed: C29.1, U11.6 (Vbst)
unnamed: C29.2, L3.1, U11.2 (SW)
unnamed: D2.2 (A), R95.1
unnamed: D3.2 (A), R96.1
unnamed: R93.2, R94.1, U11.4 (Vfb)
